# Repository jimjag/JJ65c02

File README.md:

6502 6502 6502 6502 6502 6502 6502 6502 6502 6502 6502 6502 6502 6502 6502 6502 6502
# Introduction

**JJ6502** is my own personal 6502 Single Board Computer (SBC) interpretation of the noteworthy [Ben Eater 6502 Computer](https://eater.net/6502) setup. In addition to Ben's work, I've used code, concepts and inspiration from a number of people, all acknowledged below in the **Credits** section. The ultimate inspirations are the venerable Apple II and the Atari 800 personal computers

This project contains 3 main sections:

* The actual JJ6502 breadboard computer ([Schematics](./Schematics))
* [Software](./Software)
  * The `miniOS` OS menu and ROM bootloader
  * `pico-code` : The Pi Pico (RP2040/RP2350) A/V chip (VGA driver and PS/2 keyboard interface)
  * `x65c02` Emulator
* [Documents](./Documents)

Each section has its own Readme.md and folder under this repo.

## Philosophy

More than anything, I want JJ6502 to have a retro feel. Sure, I'll use modern technology where needed, but I don't want it to be the focus of the project. I want to keep the hardware and software as authentic as possible, while still being able to take advantage of modern tools and techniques where it doesn't impact the feel and spirit of being "retro."

I am therefore putting some restrictions on the project. For example, I am limiting the video output to a 640x480 VGA screen, and the keyboard input to PS/2; graphics are bitmapped. The system is setup to encourage and foster experimentation and innovation.

Basically, I want to keep it simple and fun and recall the early days of 8-bit computing.

## Updates

Keep up to date by following the project on [Hackaday](https://hackaday.io/project/193153-jj65c02) and our [YouTube channel](https://www.youtube.com/playlist?list=PLI32OMXu1rudGl28vJc05QFXHkXWn0A19). Older notes can be found by reading the [History](./HISTORY.md) file, which served as a running log of additions and improvements.

## Pull Requests

If you would like to see any particular feature I would be happy to accept any actual code contributions via Pull Requests, or even Enhancement requests. I am happy to screen, test and merge any valuable PR.

## Contact

You can, of course, contact me via the normal Github development methods, such as Issues, Pull Requests, etc. You can also ping me via [Email](mailto:jimjag@gmail.com) and follow me/DM me on [Twitter](https://twitter.com/jimjag/)

## Credits

* Specific content noted in their respective sections
* All the helpful peeps on reddit r/beneater/

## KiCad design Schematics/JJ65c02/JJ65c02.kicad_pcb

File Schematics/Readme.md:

# JJ6502 : jimjag's 65c02 Breadboard Computer

Based on [Ben Eaters 6502 Computer](https://eater.net/6502), aka BE6502, this is my own take on his system, following in the long trend of others who have found inspiration and fun due to Ben's work.

There is no way that I could do justice to the insightful education that Ben provides in his videos, and so I won't even try. I encourage you to watch Ben's videos to get the background on his setup and his design choices. Only then will my changes make any sense...

Back? Good! Just jump in.

## What's different?

So starting from Ben's design (as of Sept. 2021), here's a partial list of modifications I've made:

* Different memory map, including bankable RAM
* Console terminal
* Dependent on 65c02 chip (not "generic" 6502)
* Added W65c51 ACIA chip and TTL-serial converter.
* Video/Audio/PS2 Keyboard interface via RP2040/RP2350 (Pi Pico)

Let's look at each in more detail.

### Memory Map
Ben's design uses a simple but functional address decoder design for his setup. The issue is that it wastes a _lot_ of memory. When all you have to work with is 64k, shared between RAM, ROM and I/O, each byte is precious.

For me, I wanted as much RAM as possible, then as much ROM as I could have, and just a little bit of I/O space.

The design I came up with requires the use of the ATF22V10C PLD for decoding. With this new address decoder, we get a much more agreeable memory map:

```
 $0000 - $9fff      RAM: 40k
   $0000 - $00ff      RAM: Zero Page
   $0100 - $01ff      RAM: Stack pointer (sp) / Page 1
   $0200 - $03ff      RAM: Bootloader set-aside / Page 2
   $0400 - $9fff      RAM: Runnable code area
   $8000 - $9fff      RAM: Bankable/swappable 8k segment
 $a000 - $afff      IO: 4k
   $a010 - $a01f      ACIA
   $a020 - $a02f      VIA
   $a800              Pi Pico
 $b000 - $ffff      ROM: 20k
```

This allows for a pretty sizable ROM-based loader and even OS, as well as extremely large (for a 6502) RAM-based code.

Because of this, Ben's code will not run unmodified on the JJ6502, but the changes are minimal. And easy.

### 65C02
Ben's design, of course, also uses the 65C02, in fact, the WDC65C02. However his code doesn't use any of the newer opcodes which this later version of the chip provides (like **PHY**). I've decided that as long as we are using the newer chip, we should take not only hardware but software advantage of that. This means, for example, that whatever assembler you use must honor the 65C02 opcode set. For `vasm`, this means you'll need to assemble with `vasm6502_oldstyle -wdc02 -dotdir -Fbin`

### Serial Support
Adding the `W65c51` ACIA chip and the `Max232` TTL-Serial
converter board allows for true RS232 terminal support,
vital for bootloader support.

## Schematics
All schematics are in the `JJ65c02` folder and use `KiCad`.

## Design
The Design Philosophy is based on being as true as possible to the concept of retro computing, while still being practical. We take advantage of modern technology only where it doesn't compromise on the "retro nature" of the system.

For example, as will be noted below, we use a Pi Pico as an I/O support chip. Now the Pico is an extremely powerful microcontroller; one look at the demos associated with the RP2040/2350, especially those around its graphics capability, show that it would be easy and tempting to offload _all_ those functions to the Pico. To me, however, that would be cheating. I wanted the system to be a 6502 which just happens to use a Pi Pico, not a Pi Pico that just happens to have a 6502.

The SBC is based around a WDC65C02, and uses the same pinout as the original 6502, but with the newer 65C02 opcodes. The design also includes a WDC65C22 VIA chip for additional I/O capabilities, and a WDC65C51 ACIA chip for serial support. All these chips support much higher clock speeds than the original 6502, and the system itself runs at 8MHz and at 5Vdc.

As noted, a Pi Pico (actually the Pico 2 at this time), is used to drive the VGA monitor and the PS2 keyboard which serve as the system _console_. PS2 key codes are sent to the 6502 via the VIA chip, but are limited to 7 bits. Since the system is ASCII based, this is not an issue (the reason why we only send 7 bits is due to not having enough GPIO pins on the Pico). The Pico "answers" on the system at address $A200 and uses the full 8 data bits.

Some of the complexity of the design is due to the level mismatch between the 6502 (et.al.) and the Pico, since the Pico itself runs on 3.3Vdc. We could run the 6502 also at 3.3, but that still would not solve all issues. To address this problem, we use line level converters as needed between the 2 voltages. When talking to the Pico, we actually latch the WRITE data, to ensure that the Pico has the time to read and process the data before the DATA bus goes unstable. All communication from the Pico is, as noted, driven by the VIA chip and interupts.

Running at 8Mhz, a standard EEPROM is simply too slow. There are a few ways of handling this, including clock stretching. I opted for using a `SST39SF010` 128K NOR Flash, which behaves like a super fast EEPROM and is programmed the exact same way. The current design however wastes a lot of that memory, since we only use 20K of its 128K capability. ROM banking is a possible future enhancement.

For the RAM, I selected the `AS6C1008` 128K SRAM chip. It is fast enough to easily handling the 8Mhz system clock speed, and provides for extra RAM via banking. The RAM banking itself is determine via the value on `Port B` of the VIA chip, and is user selectable. There are a total of 7 8K banks currently.

A `FT234XD` RS232 chip with USB output is driven by the ACIA chip to provide terminal (or "tty") communication at `19200-8N1` with hardware flow control. Sound output is line level and provided by a standard audio jack. Power is provided by a USBC connector at 5Vdc which is then also converted to 3.3Vdc with the 2 power buses being routed on the board.

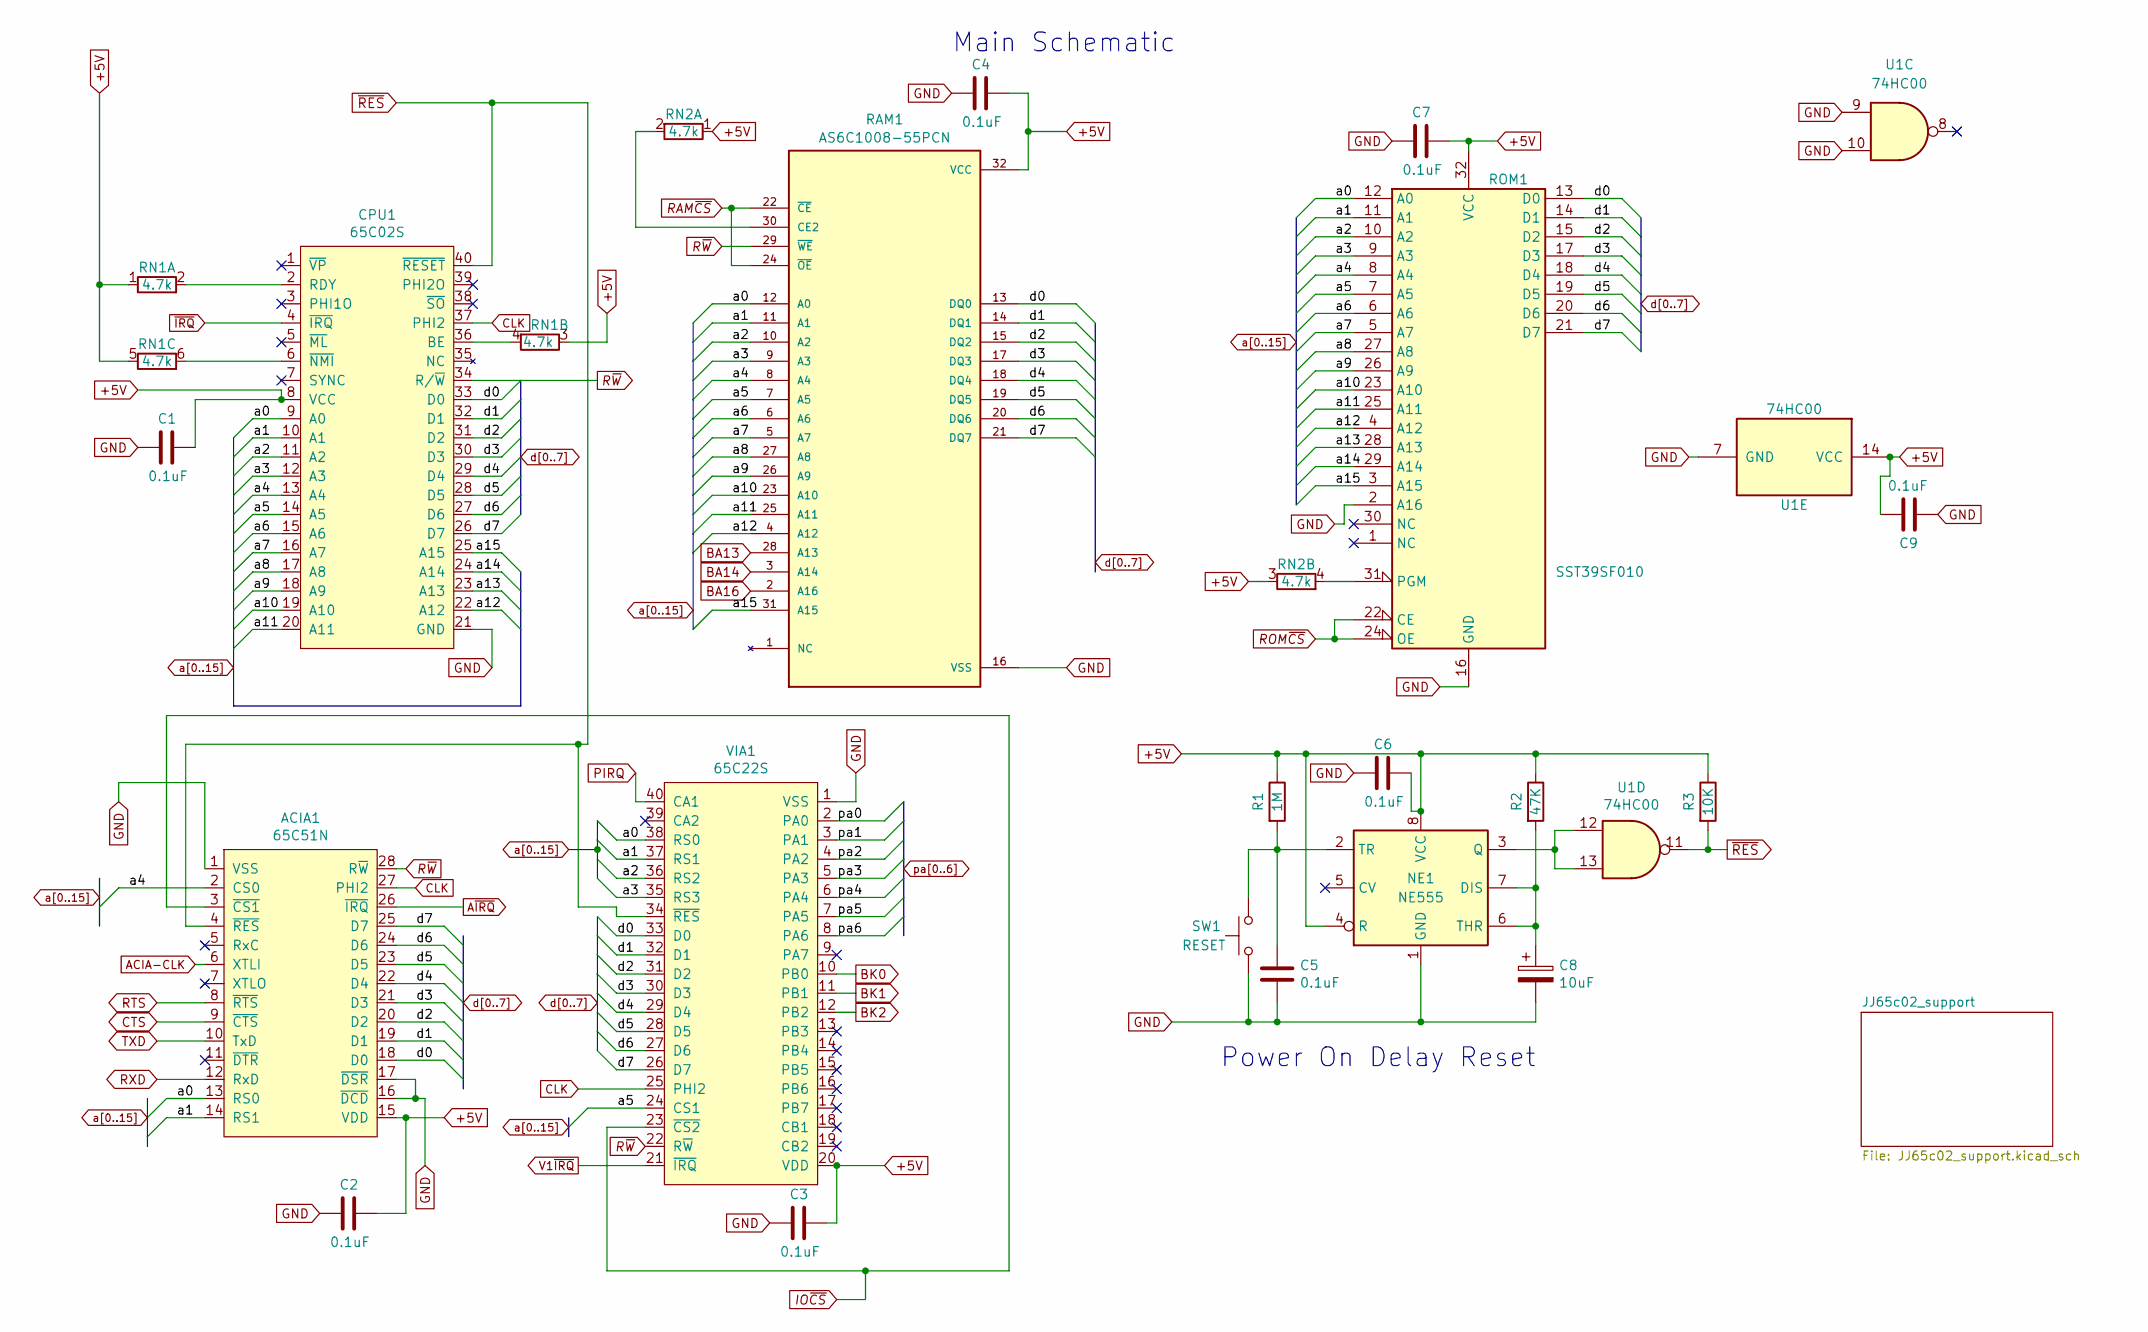
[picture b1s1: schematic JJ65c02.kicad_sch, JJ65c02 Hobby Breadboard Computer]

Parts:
ACIA1: 65C51N; DIP-28_W15.24mm_Socket
C1, C2, C3, C4, C5, C6, C7, C9: 0.1uF; C_Disc_D4.7mm_W2.5mm_P5.00mm
C8: 10uF; CP_Radial_D5.0mm_P2.50mm
CPU1: 65C02S; DIP-40_W15.24mm_Socket
NE1: NE555; DIP-8_W7.62mm
R1: 1M; R_Axial_DIN0207_L6.3mm_D2.5mm_P7.62mm_Horizontal
R2: 47K; R_Axial_DIN0207_L6.3mm_D2.5mm_P7.62mm_Horizontal
R3: 10K; R_Axial_DIN0207_L6.3mm_D2.5mm_P7.62mm_Horizontal
RAM1: AS6C1008-55PCN; DIP-32_W15.24mm_Socket; PARTREV v1.0
RN1, RN2: 4.7k; R_Array_SIP6
ROM1: SST39SF010; DIP-32_W15.24mm_Socket
SW1: RESET; SW_PUSH_6mm
U1: 74HC00; DIP-14_W7.62mm_Socket
VIA1: 65C22S; DIP-40_W15.24mm_Socket

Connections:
+5V: ACIA1.15 (VDD), C1.1, C2.1, C3.1, C4.1, C6.1, C7.1, C9.1, CPU1.8 (VCC), NE1.4 (R), NE1.8 (VCC), R1.1, R2.1, R3.1, RAM1.32 (VCC), RN1.1 (R1.1), RN1.3 (R2.1), RN1.5 (R3.1), RN2.1 (R1.1), RN2.3 (R2.1), ROM1.32 (VCC), U1.14 (VCC), VIA1.20 (VDD); also elsewhere on the board
ACIA-CLK: ACIA1.6 (XTLI); also elsewhere on the board
A~IRQ: ACIA1.26 (~IRQ); also elsewhere on the board
BA13: RAM1.28 (A13); also elsewhere on the board
BA14: RAM1.3 (A14); also elsewhere on the board
BA16: RAM1.2 (A16); also elsewhere on the board
BK0: VIA1.10 (PB0); also elsewhere on the board
BK1: VIA1.11 (PB1); also elsewhere on the board
BK2: VIA1.12 (PB2); also elsewhere on the board
CLK: ACIA1.27 (PHI2), CPU1.37 (PHI2), VIA1.25 (PHI2); also elsewhere on the board
CTS: ACIA1.9 (~CTS); also elsewhere on the board
GND: ACIA1.1 (VSS), ACIA1.16 (~DCD), ACIA1.17 (~DSR), C1.2, C2.2, C3.2, C4.2, C5.2, C6.2, C7.2, C8.2, C9.2, CPU1.21 (GND), NE1.1 (GND), RAM1.16 (VSS), ROM1.2 (A16), ROM1.16 (GND), SW1.1, U1.7 (GND), U1.9, U1.10, VIA1.1 (VSS); also elsewhere on the board
IO~CS: ACIA1.3 (~CS1), VIA1.23 (~CS2); also elsewhere on the board
unnamed: CPU1.36 (BE), RN1.4 (R2.2)
unnamed: CPU1.2 (RDY), RN1.2 (R1.2)
unnamed: CPU1.6 (~NMI), RN1.6 (R3.2)
unnamed: C8.1, NE1.6 (THR), NE1.7 (DIS), R2.2
unnamed: NE1.3 (Q), U1.12, U1.13
unnamed: C5.1, NE1.2 (TR), R1.2, SW1.2
unnamed: RAM1.30 (CE2), RN2.2 (R1.2)
unnamed: RN2.4 (R2.2), ROM1.31 (PGM)
PIRQ: VIA1.40 (CA1); also elsewhere on the board
RAM~CS: RAM1.22 (~CE), RAM1.24 (~OE); also elsewhere on the board
ROM~CS: ROM1.22 (CE), ROM1.24 (OE); also elsewhere on the board
RTS: ACIA1.8 (~RTS); also elsewhere on the board
RXD: ACIA1.12 (RxD); also elsewhere on the board
R~W: ACIA1.28 (R~W), CPU1.34 (R/~W), RAM1.29 (~WE), VIA1.22 (R~W); also elsewhere on the board
TXD: ACIA1.10 (TxD); also elsewhere on the board
V1~IRQ: VIA1.21 (~IRQ); also elsewhere on the board
a0: ACIA1.13 (RS0), CPU1.9 (A0), RAM1.12 (A0), ROM1.12 (A0), VIA1.38 (RS0)
a1: ACIA1.14 (RS1), CPU1.10 (A1), RAM1.11 (A1), ROM1.11 (A1), VIA1.37 (RS1)
a2: CPU1.11 (A2), RAM1.10 (A2), ROM1.10 (A2), VIA1.36 (RS2)
a3: CPU1.12 (A3), RAM1.9 (A3), ROM1.9 (A3), VIA1.35 (RS3)
a4: ACIA1.2 (CS0), CPU1.13 (A4), RAM1.8 (A4), ROM1.8 (A4)
a5: CPU1.14 (A5), RAM1.7 (A5), ROM1.7 (A5), VIA1.24 (CS1)
a6: CPU1.15 (A6), RAM1.6 (A6), ROM1.6 (A6)
a7: CPU1.16 (A7), RAM1.5 (A7), ROM1.5 (A7)
a8: CPU1.17 (A8), RAM1.27 (A8), ROM1.27 (A8)
a9: CPU1.18 (A9), RAM1.26 (A9), ROM1.26 (A9)
a10: CPU1.19 (A10), RAM1.23 (A10), ROM1.23 (A10)
a11: CPU1.20 (A11), RAM1.25 (A11), ROM1.25 (A11); also elsewhere on the board
a12: CPU1.22 (A12), RAM1.4 (A12), ROM1.4 (A12); also elsewhere on the board
a13: CPU1.23 (A13), ROM1.28 (A13); also elsewhere on the board
a14: CPU1.24 (A14), ROM1.29 (A14); also elsewhere on the board
a15: CPU1.25 (A15), RAM1.31 (A15), ROM1.3 (A15); also elsewhere on the board
d0: ACIA1.18 (D0), CPU1.33 (D0), RAM1.13 (DQ0), ROM1.13 (D0), VIA1.33 (D0); also elsewhere on the board
d1: ACIA1.19 (D1), CPU1.32 (D1), RAM1.14 (DQ1), ROM1.14 (D1), VIA1.32 (D1); also elsewhere on the board
d2: ACIA1.20 (D2), CPU1.31 (D2), RAM1.15 (DQ2), ROM1.15 (D2), VIA1.31 (D2); also elsewhere on the board
d3: ACIA1.21 (D3), CPU1.30 (D3), RAM1.17 (DQ3), ROM1.17 (D3), VIA1.30 (D3); also elsewhere on the board
d4: ACIA1.22 (D4), CPU1.29 (D4), RAM1.18 (DQ4), ROM1.18 (D4), VIA1.29 (D4); also elsewhere on the board
d5: ACIA1.23 (D5), CPU1.28 (D5), RAM1.19 (DQ5), ROM1.19 (D5), VIA1.28 (D5); also elsewhere on the board
d6: ACIA1.24 (D6), CPU1.27 (D6), RAM1.20 (DQ6), ROM1.20 (D6), VIA1.27 (D6); also elsewhere on the board
d7: ACIA1.25 (D7), CPU1.26 (D7), RAM1.21 (DQ7), ROM1.21 (D7), VIA1.26 (D7); also elsewhere on the board
pa0: VIA1.2 (PA0); also elsewhere on the board
pa1: VIA1.3 (PA1); also elsewhere on the board
pa2: VIA1.4 (PA2); also elsewhere on the board
pa3: VIA1.5 (PA3); also elsewhere on the board
pa4: VIA1.6 (PA4); also elsewhere on the board
pa5: VIA1.7 (PA5); also elsewhere on the board
pa6: VIA1.8 (PA6); also elsewhere on the board
~IRQ: CPU1.4 (~IRQ); also elsewhere on the board
~RES: ACIA1.4 (~RES), CPU1.40 (~RESET), R3.2, U1.11, VIA1.34 (~RES)

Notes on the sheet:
Main Schematic
Power On Delay Reset

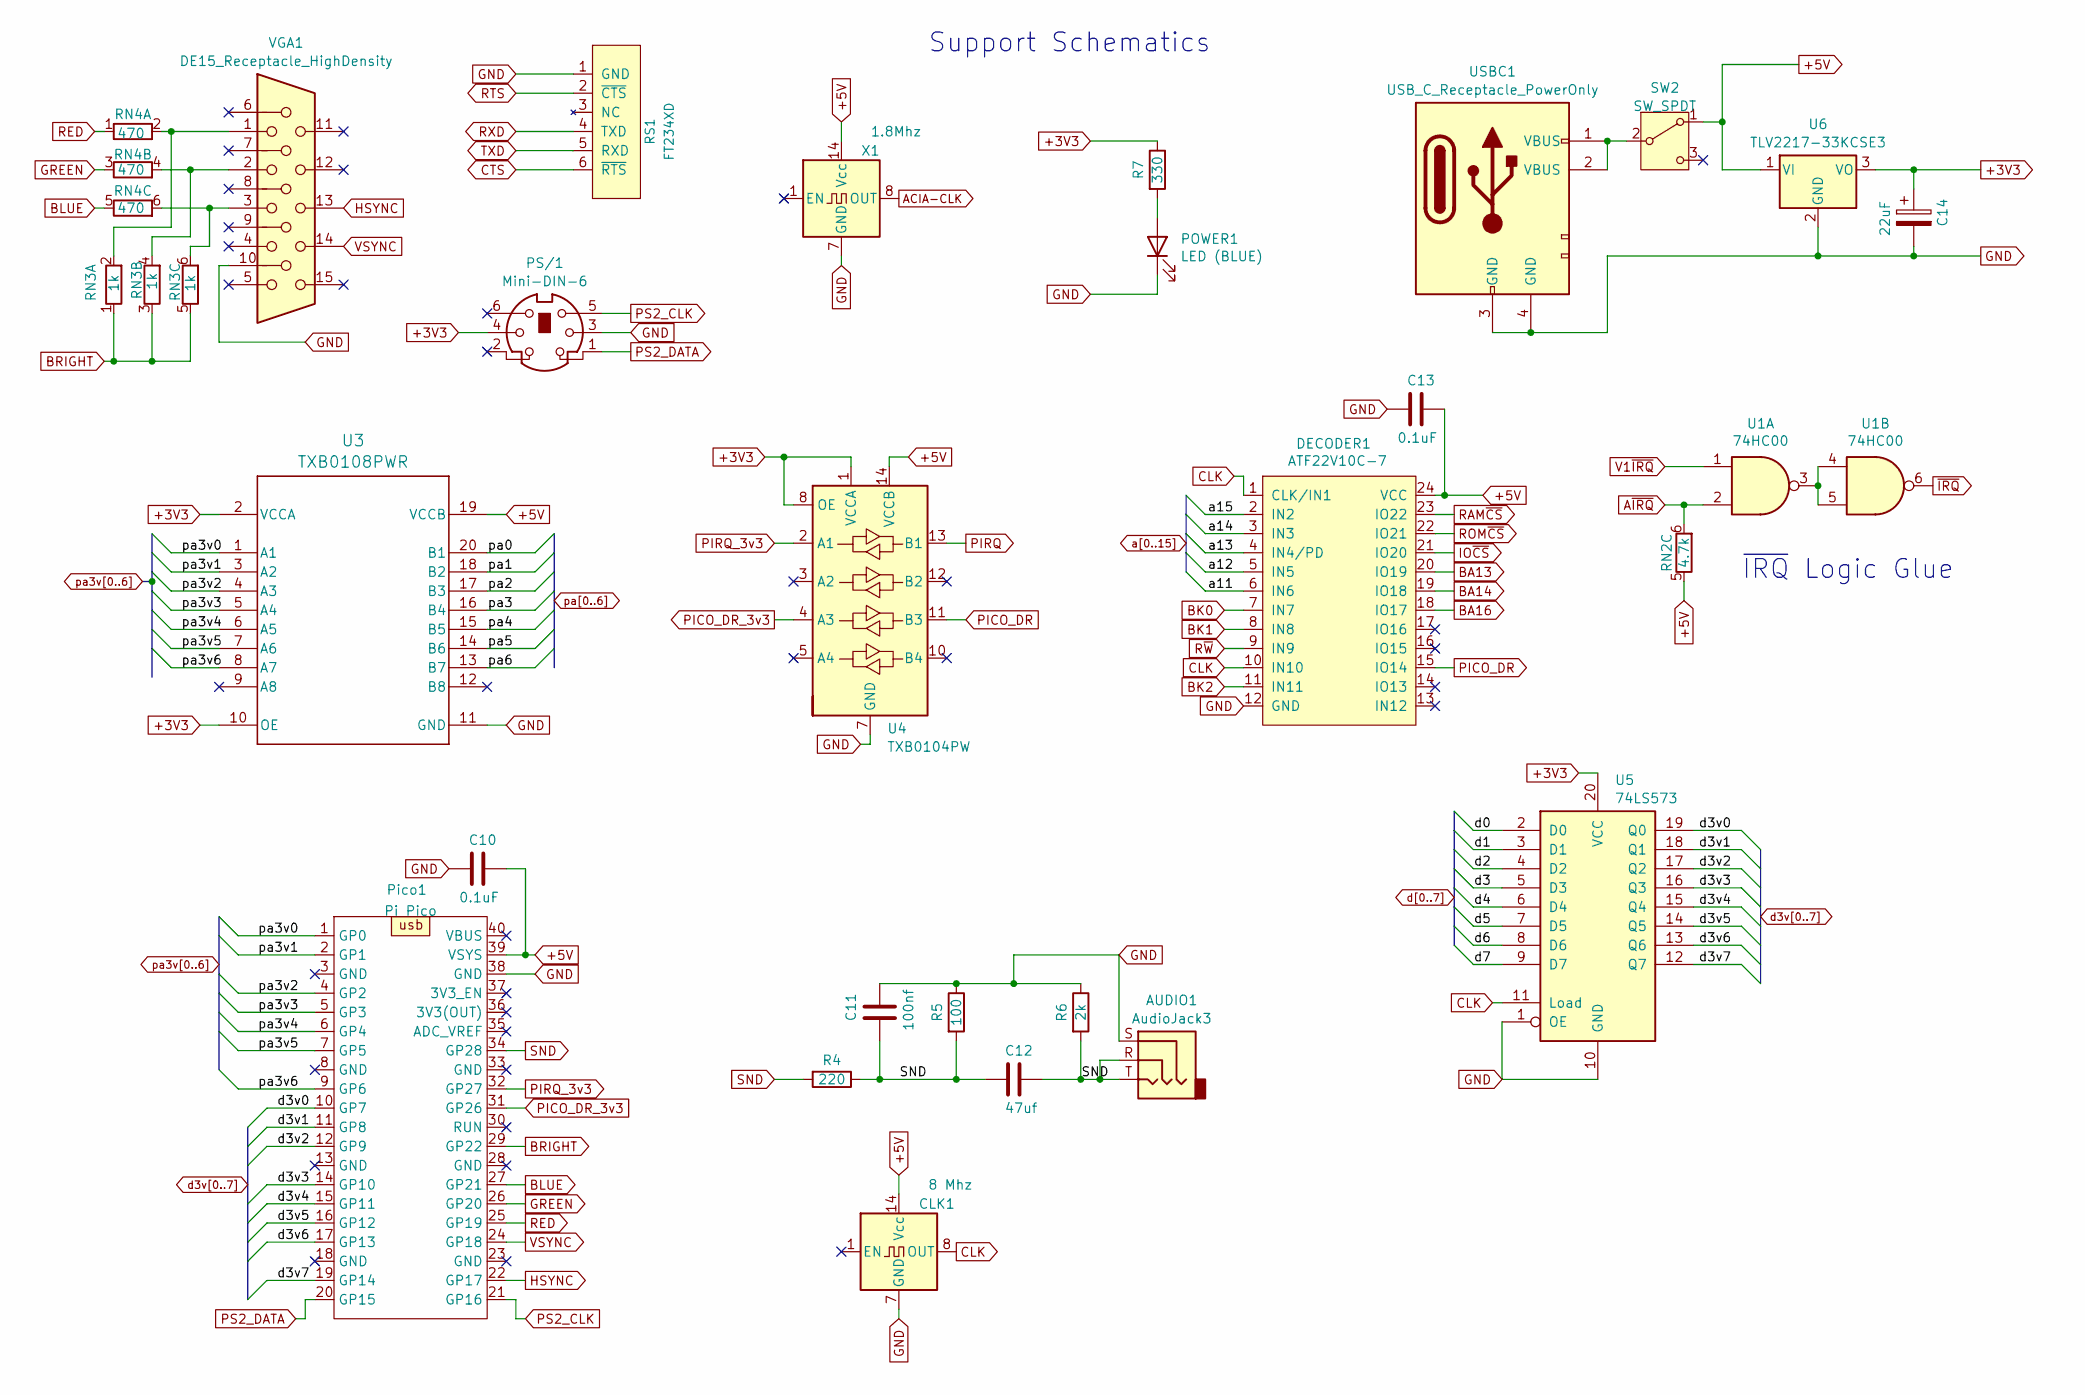
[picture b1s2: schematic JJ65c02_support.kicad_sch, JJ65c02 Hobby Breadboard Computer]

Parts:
AUDIO1: AudioJack3; Jack_3.5mm_CUI_SJ1-3533NG_Horizontal
C10, C13: 0.1uF; C_Disc_D4.7mm_W2.5mm_P5.00mm
C11: 100nf; C_Disc_D4.7mm_W2.5mm_P5.00mm
C12: 47uf; C_Disc_D4.7mm_W2.5mm_P5.00mm
C14: 22uF; CP_Radial_D6.3mm_P2.50mm
CLK1: 8 Mhz; Oscillator_DIP-14
DECODER1: ATF22V10C-7; DIP-24_W7.62mm_Socket
POWER1: LED (BLUE); LED_D3.0mm_FlatTop
PS/1: Mini-DIN-6; mini_din-6
Pico1: Pi Pico; Raspberry_pi_pico
R4: 220; R_Axial_DIN0207_L6.3mm_D2.5mm_P7.62mm_Horizontal
R5: 100; R_Axial_DIN0207_L6.3mm_D2.5mm_P7.62mm_Horizontal
R6: 2k; R_Axial_DIN0207_L6.3mm_D2.5mm_P7.62mm_Horizontal
R7: 330; R_Axial_DIN0207_L6.3mm_D2.5mm_P7.62mm_Horizontal
RN2: 4.7k; R_Array_SIP6
RN3: 1k; R_Array_SIP6
RN4: 470; R_Array_SIP6
RS1: FT234XD; TerminalBlock_TE_282834-6_1x06_P2.54mm_Horizontal
SW2: SW_SPDT
U1: 74HC00; DIP-14_W7.62mm_Socket
U3: TXB0108PWR; TSSOP-20_4.4x6.5mm_P0.65mm
U4: TXB0104PW; SOIC-14_3.9x8.7mm_P1.27mm
U5: 74LS573; SOIC-20W_7.5x12.8mm_P1.27mm
U6: TLV2217-33KCSE3; TO-220-3_Vertical
USBC1: USB_C_Receptacle_PowerOnly; USBC_power
VGA1: DE15_Receptacle_HighDensity; CONN_HDE15P_AMP
X1: 1.8Mhz; Oscillator_DIP-14

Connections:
+3V3: C14.1, PS/1.4, R7.1, U3.2 (VCCA), U3.10 (OE), U4.1 (VCCA), U4.8 (OE), U5.20 (VCC), U6.3 (VO)
+5V: C10.1, C13.1, CLK1.14 (Vcc), DECODER1.24 (VCC), Pico1.39 (VSYS), RN2.5 (R3.1), SW2.1 (A), U3.19 (VCCB), U4.14 (VCCB), U6.1 (VI), X1.14 (Vcc); also elsewhere on the board
ACIA-CLK: X1.8 (OUT); also elsewhere on the board
A~IRQ: RN2.6 (R3.2), U1.2; also elsewhere on the board
BA13: DECODER1.20 (IO19); also elsewhere on the board
BA14: DECODER1.19 (IO18); also elsewhere on the board
BA16: DECODER1.18 (IO17); also elsewhere on the board
BK0: DECODER1.7 (IN7); also elsewhere on the board
BK1: DECODER1.8 (IN8); also elsewhere on the board
BK2: DECODER1.11 (IN11); also elsewhere on the board
BLUE: Pico1.27 (GP21), RN4.5 (R3.1); also elsewhere on the board
BRIGHT: Pico1.29 (GP22), RN3.1 (R1.1), RN3.3 (R2.1), RN3.5 (R3.1); also elsewhere on the board
CLK: CLK1.8 (OUT), DECODER1.1 (CLK/IN1), DECODER1.10 (IN10), U5.11 (Load); also elsewhere on the board
CTS: RS1.6 (~RTS); also elsewhere on the board
GND: AUDIO1.S, C10.2, C11.1, C13.2, C14.2, CLK1.7 (GND), DECODER1.12 (GND), POWER1.1 (K), PS/1.3, Pico1.38 (GND), R5.1, R6.1, RS1.1 (GND), U3.11 (GND), U4.7 (GND), U5.1 (OE), U5.10 (GND), U6.2 (GND), USBC1.3 (GND), USBC1.4 (GND), VGA1.10, X1.7 (GND); also elsewhere on the board
GREEN: Pico1.26 (GP20), RN4.3 (R2.1); also elsewhere on the board
HSYNC: Pico1.22 (GP17), VGA1.13; also elsewhere on the board
IO~CS: DECODER1.21 (IO20); also elsewhere on the board
unnamed: POWER1.2 (A), R7.2
unnamed: RN3.2 (R1.2), RN4.2 (R1.2), VGA1.1
unnamed: RN3.4 (R2.2), RN4.4 (R2.2), VGA1.2
unnamed: RN3.6 (R3.2), RN4.6 (R3.2), VGA1.3
unnamed: SW2.2 (B), USBC1.1 (VBUS), USBC1.2 (VBUS)
unnamed: U1.3, U1.4, U1.5
PICO_DR: DECODER1.15 (IO14), U4.11 (B3)
PICO_DR_3v3: Pico1.31 (GP26), U4.4 (A3); also elsewhere on the board
PIRQ: U4.13 (B1); also elsewhere on the board
PIRQ_3v3: Pico1.32 (GP27), U4.2 (A1); also elsewhere on the board
PS2_CLK: PS/1.5, Pico1.21 (GP16); also elsewhere on the board
PS2_DATA: PS/1.1, Pico1.20 (GP15); also elsewhere on the board
RAM~CS: DECODER1.23 (IO22); also elsewhere on the board
RED: Pico1.25 (GP19), RN4.1 (R1.1); also elsewhere on the board
ROM~CS: DECODER1.22 (IO21); also elsewhere on the board
RTS: RS1.2 (~CTS); also elsewhere on the board
RXD: RS1.4 (TXD); also elsewhere on the board
R~W: DECODER1.9 (IN9); also elsewhere on the board
SND: AUDIO1.R, AUDIO1.T, C11.2, C12.1, C12.2, Pico1.34 (GP28), R4.1, R4.2, R5.2, R6.2; also elsewhere on the board
TXD: RS1.5 (RXD); also elsewhere on the board
V1~IRQ: U1.1; also elsewhere on the board
VSYNC: Pico1.24 (GP18), VGA1.14; also elsewhere on the board
a11: DECODER1.6 (IN6); also elsewhere on the board
a12: DECODER1.5 (IN5); also elsewhere on the board
a13: DECODER1.4 (IN4/PD); also elsewhere on the board
a14: DECODER1.3 (IN3); also elsewhere on the board
a15: DECODER1.2 (IN2); also elsewhere on the board
d0: U5.2 (D0); also elsewhere on the board
d1: U5.3 (D1); also elsewhere on the board
d2: U5.4 (D2); also elsewhere on the board
d3: U5.5 (D3); also elsewhere on the board
d3v0: Pico1.10 (GP7), U5.19 (Q0); also elsewhere on the board
d3v1: Pico1.11 (GP8), U5.18 (Q1); also elsewhere on the board
d3v2: Pico1.12 (GP9), U5.17 (Q2); also elsewhere on the board
d3v3: Pico1.14 (GP10), U5.16 (Q3); also elsewhere on the board
d3v4: Pico1.15 (GP11), U5.15 (Q4); also elsewhere on the board
d3v5: Pico1.16 (GP12), U5.14 (Q5); also elsewhere on the board
d3v6: Pico1.17 (GP13), U5.13 (Q6); also elsewhere on the board
d3v7: Pico1.19 (GP14), U5.12 (Q7); also elsewhere on the board
d4: U5.6 (D4); also elsewhere on the board
d5: U5.7 (D5); also elsewhere on the board
d6: U5.8 (D6); also elsewhere on the board
d7: U5.9 (D7); also elsewhere on the board
pa0: U3.20 (B1); also elsewhere on the board
pa1: U3.18 (B2); also elsewhere on the board
pa2: U3.17 (B3); also elsewhere on the board
pa3: U3.16 (B4); also elsewhere on the board
pa3v0: Pico1.1 (GP0), U3.1 (A1); also elsewhere on the board
pa3v1: Pico1.2 (GP1), U3.3 (A2); also elsewhere on the board
pa3v2: Pico1.4 (GP2), U3.4 (A3); also elsewhere on the board
pa3v3: Pico1.5 (GP3), U3.5 (A4); also elsewhere on the board
pa3v4: Pico1.6 (GP4), U3.6 (A5); also elsewhere on the board
pa3v5: Pico1.7 (GP5), U3.7 (A6); also elsewhere on the board
pa3v6: Pico1.9 (GP6), U3.8 (A7); also elsewhere on the board
pa4: U3.15 (B5); also elsewhere on the board
pa5: U3.14 (B6); also elsewhere on the board
pa6: U3.13 (B7); also elsewhere on the board
~IRQ: U1.6; also elsewhere on the board

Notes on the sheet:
Support Schematics
~{IRQ} Logic Glue

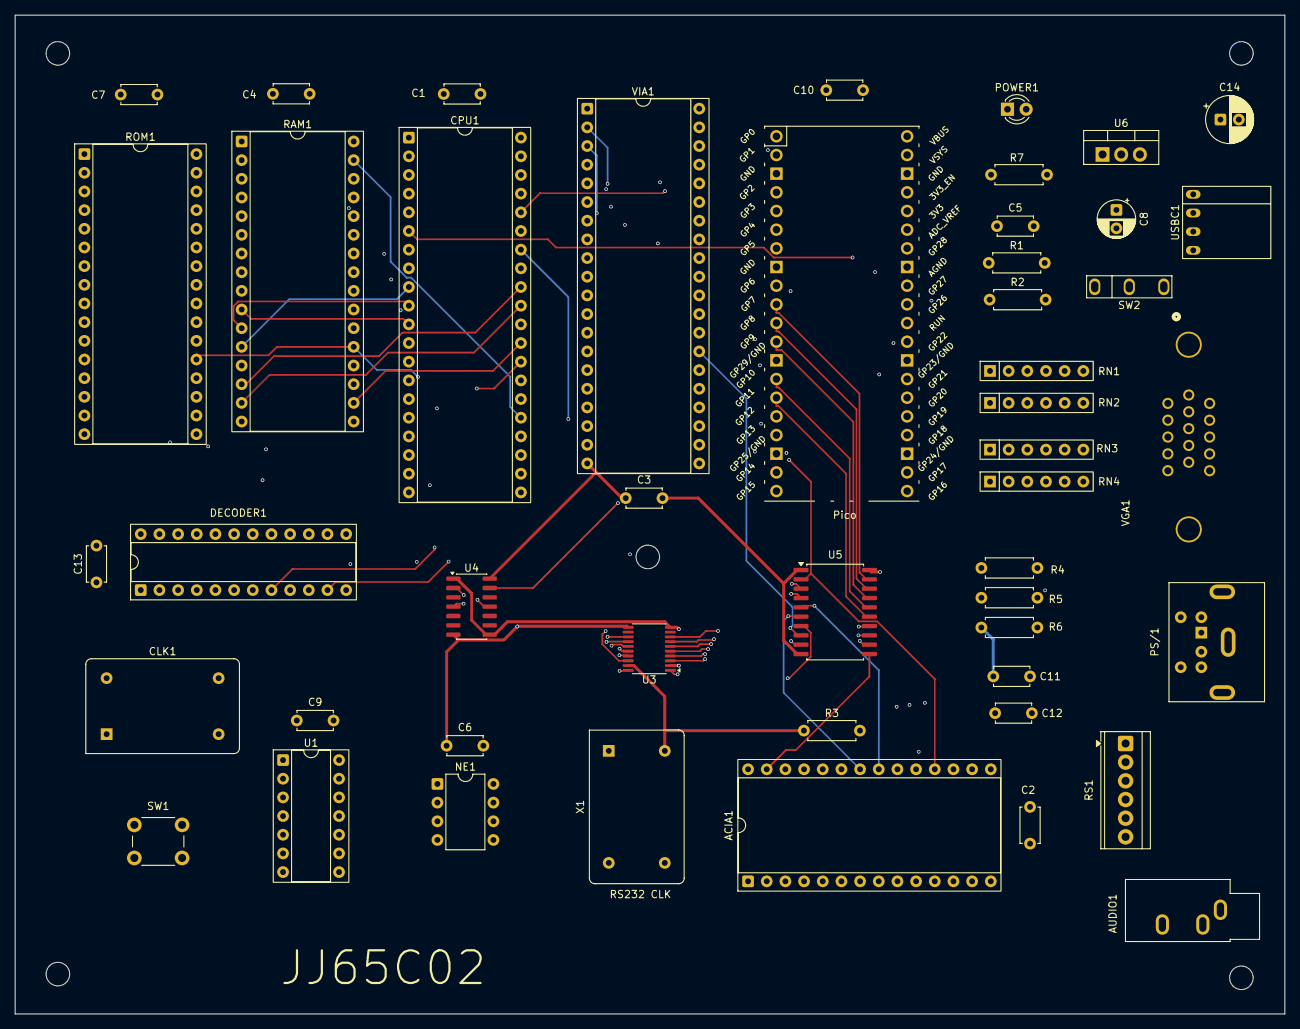
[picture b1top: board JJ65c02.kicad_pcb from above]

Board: 4 copper layers, 172.7 x 135.9 mm, 53 parts (1 on the bottom side), 96 nets.

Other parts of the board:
PH1, PH2, PH3, PH4, PH5: MountingHole_3.2mm_M3_DIN965
Pico: Pico; RPi_Pico_SMD_TH

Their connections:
+5V: Pico.39 (VSYS); also elsewhere on the board
BLUE: Pico.27 (GPIO21); also elsewhere on the board
BRIGHT: Pico.29 (GPIO22); also elsewhere on the board
GND: Pico.38 (GND); also elsewhere on the board
GREEN: Pico.26 (GPIO20); also elsewhere on the board
HSYNC: Pico.22 (GPIO17); also elsewhere on the board
PICO_DR_3v3: Pico.31 (GPIO26_ADC0); also elsewhere on the board
PIRQ_3v3: Pico.32 (GPIO27_ADC1); also elsewhere on the board
PS2_CLK: Pico.21 (GPIO16); also elsewhere on the board
PS2_DATA: Pico.20 (GPIO15); also elsewhere on the board
RED: Pico.25 (GPIO19); also elsewhere on the board
SND: Pico.34 (GPIO28_ADC2); also elsewhere on the board
VSYNC: Pico.24 (GPIO18); also elsewhere on the board
d3v0: Pico.10 (GPIO7); also elsewhere on the board
d3v1: Pico.11 (GPIO8); also elsewhere on the board
d3v2: Pico.12 (GPIO9); also elsewhere on the board
d3v3: Pico.14 (GPIO10); also elsewhere on the board
d3v4: Pico.15 (GPIO11); also elsewhere on the board
d3v5: Pico.16 (GPIO12); also elsewhere on the board
d3v6: Pico.17 (GPIO13); also elsewhere on the board
d3v7: Pico.19 (GPIO14); also elsewhere on the board
pa3v0: Pico.1 (GPIO0); also elsewhere on the board
pa3v1: Pico.2 (GPIO1); also elsewhere on the board
pa3v2: Pico.4 (GPIO2); also elsewhere on the board
pa3v3: Pico.5 (GPIO3); also elsewhere on the board
pa3v4: Pico.6 (GPIO4); also elsewhere on the board
pa3v5: Pico.7 (GPIO5); also elsewhere on the board
pa3v6: Pico.9 (GPIO6); also elsewhere on the board

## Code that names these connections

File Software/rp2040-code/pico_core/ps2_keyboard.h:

#ifndef P2_KEYBOARD_H_
#define P2_KEYBOARD_H_
#include "hardware/clocks.h"
#include "hardware/dma.h"
#include "hardware/pio.h"
#include "hardware/gpio.h"
#include "pico/stdlib.h"
#include <stdio.h>
#include <stdlib.h>

#define PS2FREQ   133600.0f

// GPIO pins to VIA chip
enum ps2_pins {PA0=0, PA1, PA2, PA3, PA4, PA5, PA6, PS2_DATA_PIN=15, PS2_CLK_PIN, PIRQ=27};

void initPS2(void);
unsigned char ps2GetChar(bool auto_print);
unsigned char ps2GetCharBlk(bool auto_print);
void clearPS2(void);
void ps2Task(bool auto_print);

#endif // P2_KEYBOARD_H_

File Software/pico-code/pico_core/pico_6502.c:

/**
 * MIT License
 * Copyright (c) 2021-2024 Jim Jagielski
 */
/**
 *
 * HARDWARE CONNECTIONS
 *  - GPIO 17 ---> VGA Hsync
 *  - GPIO 18 ---> VGA Vsync
 *  - GPIO 19 ---> 470 ohm resistor ---> VGA Red
 *  - GPIO 20 ---> 470 ohm resistor ---> VGA Green
 *  - GPIO 21 ---> 470 ohm resistor ---> VGA Blue
 *  - GPIO 22 ---> 1k ohm resistor ---> VGA Intensity (bright)
 *  - GPIO 15 ---> PS2 Data pin
 *  - GPIO 16 ---> PS2 Clock pin
 *  - RP2040 GND ---> VGA GND
 *  - GPIO 0-6 ---> 7 bit PS/2 Data to VIA
 *  - GPIO 7-14 ---> 8 Bit Data In from 6502
 *  - GPIO 26 ---> Data Ready
 *  - GPIO 27 ---> IRQ/Handshake to VIA for PS/2
 *  - GPIO 28 ---> audio/sound
 *
 * RESOURCES USED
 *  CORE 0
 *  - VGA:
 *  -   PIO state machines 0, 1, and 2 on PIO instance 0
 *  -   DMA channels 0, 1, 2, and 3
 *  -   IRQ 0, 1
 *  -   153.6 kBytes of RAM (for pixel color data)
 *  - PS2:
 *  -   PIO state machine 0 on PIO instance 1
 *  -   IRQ 1
 *  - MEMIN:
 *  -   PIO state machine 1 on PIO instance 1
 *  -   IRQ 0
 *
 * CORE 1
 * - SND:
 * -   PWM
 */

#ifdef HOST_SIM
// Host SDL simulation: the Pico SDK, PS/2 driver and sound synth are replaced
// by the shims in sim/pico_shim.h (see sim/README.md). This is the same file
// the RP2350 runs; only the hardware layer differs.
#include "../sim/pico_shim.h"
#include "vga_core.h"
#include <stdio.h>
#include <stdlib.h>
#else
#include <stdio.h>
#include <stdlib.h>
#include "pico/stdlib.h"
#include "hardware/pio.h"
#include "hardware/dma.h"
#include "pico/multicore.h"
#include "vga_core.h"
#include "ps2_keyboard.h"
#include "pico_synth_ex.h"
#endif

void core1_main() {
    initPS2();
    clearPS2();
    initSOUND();
    startup_chord();
    while (true) {
        soundTask();
        ps2Task(false);
        //tight_loop_contents();
    }
}

#ifdef HOST_SIM
// The SDL viewer owns the process main thread (macOS requires the Cocoa event
// loop there) and runs this on a worker thread instead of main().
int demo_main()
#else
int main()
#endif
{
    // rp2350 will run at 300 Mhz at 1.3 volt
    // vreg_set_voltage (VREG_VOLTAGE_1_30);
    //vreg_set_voltage(VREG_VOLTAGE_1_15);
    set_sys_clock_khz(300000, true);
    // Initialize stdio
    //stdio_init_all();

    // start core 1 threads
    //multicore_reset_core1();
    multicore_launch_core1(&core1_main);
#ifdef HOST_SIM
    // Bring up the unix-socket listener; the x65c02 emulator connects and its
    // $A800 writes start arriving as the 6502 byte stream (see sim/sim_link.c).
    sim_link_start(NULL);
#endif
    // Initialize the VGA screen and PS/2 interface
    initVGA();
    //initPS2();
    //clearPS2();
    setFont(0);
    setTextColor2(WHITE, BLUE);
    setTxtCursor(0, 0);
    vgaFillScreen(BLUE);
    setCursor(65, 0);
    setTextSize(2);
    drawString(VERSION_6502);
    setTextSize(1);
    setTxtCursor(0, 3);
    enableCurs(true);
    //clearPS2();
    while (true) {
        conInTask();  // Look for incoming data
        //ps2Task(false);  // And send out any PS/2 data
        //tight_loop_contents();
    }
}

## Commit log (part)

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2023-11-19 vga_core was getting big... pull out graphics codebase to a sep file and pull it in via overloading #include instead of adjusting the actual build process to compile/link another file... after all, w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
2023-11-19 Fix blinking cursor potential corruption
2023-11-21 Use interrupts and implement a read buffer
2023-11-21 More work on WOZMON o lowercase opcodes o use CONsole I/O o Don't echo input o check for actual interrupt
2023-11-21 Compile WOZMON Remove more LCD stuff and replace w/ console i/o Use asciiz and not actual bytes since we can simply print these now
2023-11-21 Final nibs to get it compiling... likely will NOT work yet :)
2023-11-22 We're not using Terminus
2023-11-22 Make more universal (avoid hard coded magic numbers) Add blocking char/byte read Continue move from mini-keyboard to Console
2023-11-23 For timing purposes, tell the Pico to READ the data (which the 6502 as written) when the DR signal falls, which corresponds to the 6502 clock falling as well. This ensures that the data to be read is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
2023-11-24 Move to using PIO sm for reading data from the 6502
2023-11-24 Note about Tmds on 6502 which makes this dependent on the actual clock speed of the 6502... :(
2023-11-24 Remove fluff
2023-11-26 Interrupt 1. Don't pull-up these pins
2023-11-29 Update mem map for ehbasic
2023-12-08 Timing for reading from 6502 for CON output
2023-12-08 Get menus working w/ prompts and nice screen rendering
2023-12-08 Just in case the INIT does more at some point, let's just dupe it now
2023-12-08 Stability work Adjust WOZMON to output \r\n since we do not auto-adjust this in the Pico/VGA driver
2023-12-09 Make WOZMON work w/ lowercase
2023-12-12 And we will be using both YMODEM send and recv
2023-12-12 Use standard delay func
2023-12-13 Start implement of LOAD and SAVE for EhBasic using YMODEM to do the actual file and xfer work
2023-12-13 some fluff and lint
2023-12-14 Add in a "transparent" color, which is really just a flag to leave the pixel alone
2023-12-19 Start adding 6502 routines for graphics interface to Pi Pico
2023-12-19 Add in color table (as derived from Pi Pico) and export
2023-12-20 Some simplification
2023-12-20 more timing adjs
2023-12-27 Pull in correct ending address
2023-12-27 Misc clean ups
2023-12-27 Use typedefs
2023-12-28 start on sprite
2023-12-28 Avoid magic numbers when possible. Load in full sprite data. TODO: bitmap, mask, etc...
2023-12-28 Initial draw/erase impl. Does not handle any (x,y) error detection/correction nor does it handle cases where only a section of the sprite is "on screen": all or nothing
2023-12-28 Bug fix
2023-12-28 Don't shift at final loop
2023-12-29 Support USB
2023-12-29 Pre-calc shifted bitmap and mask and save some cycles during a critical time
2023-12-29 Optimize :)
2023-12-30 Use logical indexes that align w/ X ccords
2024-01-03 Update NOTICE Update clock freq for sound PWM
2024-01-05 Get cmd from cpu-cpu FIFO
2024-01-05 Start some sound capabilities... TODO: The sound demo part where we read from the PS/2 and do stuff is delaying??
2024-01-11 Adjust demo and add in change of preset ("voice") functionality
2024-01-11 Some minor fluff
2024-01-12 And these are ZP values
2024-01-23 Update to docs to latest rev of board
2024-01-25 instead of "fixing" STR$(), create CSTR$(), which is what other BASICs provide. NOTE: The arg to CSTR$() must be numeric
2024-01-26 Add in case patch
2024-01-26 Some fine-tuning of sound func
2024-01-29 Push beta1
2024-01-29 Some doc updates
2024-01-30 Additional voices
2024-01-31 comment
2024-01-31 y bounds handling... x is a LOT more complex since 1 byte == 2 pixels.
2024-02-01 Sprite works
2024-02-02 Reformat file to standards
2024-02-02 Allow for each voice to have its own sound
2024-02-02 Reformats
2024-02-03 formatting cleanup - no func changes
2024-02-05 variable height sprites
2024-02-05 Simpl the logic
2024-02-06 prep temp for 32pixel sprites and use generic func calls
2024-02-07 "Double" sprites
2024-02-07 Add some comments explaining some nuances of the sprite code
2024-02-07 Move some static data arrays into flash and save SRAM for actual changing data
2024-02-08 rough in tiles
2024-02-11 Only convert if not already converted
2024-02-11 Use enums and avoid magic numbers
2024-02-11 Update w/ new 32b sprite using color pallette
2024-02-13 Hey. We have an ugly tile!
2024-02-14 Bump to 6502 running at 5Mhz
2024-02-14 Enable RAM banking using VIA PortB bits
2024-02-15 minor ups
2024-02-16 Updated schematics for v2-pico
2024-02-18 if we are using the pi pico to generate the clock, we need to level convert from 3.3 to 5v
2024-02-23 Final rename fixes
2024-02-23 Create PIO sm for CLK/PHI signal on GPIO24
2024-02-27 Pico-2 changes (rp2040 now provides clk) and upgrade to Kicad 8.0
2024-02-28 More work on rp2040-version2
2024-02-29 Add in latest schematic
2024-03-11 More work on rp2040 updates
2024-03-15 Some fine tuning...
2024-03-15 Simplify the blinking cursor code... don't do any actually drawing in the timer callback, just update a var that the timer was triggered.
2024-03-15 We are now running at 8Mhz
2024-03-15 restore these for cases where we don't access through PrintChar()
2024-03-19 Rename to make more sense
2024-08-12 pico-sdk 2.0 is out
2024-08-13 Get building again
2024-10-28 Start doc updates
2025-01-21 Latest updates
2025-01-21 Since we support both the 2040 and the 2350, just use the generic 'pico' name
2025-07-09 Latest versions
2025-07-14 Add in required files for Kicad
2025-08-05 Restore
2025-08-05 Make note
2025-08-06 Work on releasing v2.0.0
2026-01-15 Add in WinCUPL files for programming the ATF22V10 PLD
2026-01-15 2 possible values for device depending on minipro version
2026-01-16 Standardize on ca65 syntax and use variables instead of magic numbers
2026-01-16 Rename vars for more logical names
2026-01-16 Save some zeropage memory (7 bytes!) and create a variable for determining where BASIC gets its I/O from
2026-01-16 Clean up ehbasic.c for standard formatting
2026-01-19 And more formatting - no func changes
2026-01-19 correct mistaken comment in string (actually, char)
2026-01-19 Add in 'TTY' command for EhBASIC, which switches the I/O for BASIC from the Console to the Serial Port TTY.
    Expected use:
    Enter TTY
    Use TTY terminal program to cut/paste for file listing or entry
    Enter TTY again
    Back to Console mode
2026-01-19 Some work on getting Emulator to work... if doing emulator (using a 6502 simulator), bypass some junk like checking RAM, etc...
2026-01-20 Work on emulator I/O
2026-01-20 Just sleep to control speed
2026-01-20 formatting
2026-01-20 Finish TTY command
2026-01-21 Final (ha!) touches to get TTY working
2026-01-21 Work on another program loading method: Intel HEX format
2026-01-21 Check for both \r and \n Skip inf loop if we never see a ':' - only check line len and ignore
2026-01-21 Handle branches > 128
2026-01-22 Keep track of how much the _system_ uses of ZP. Consider system usage of ZP memory as protected memory, unavailable for re-use. We may eventually need to reuse ZP memory in large portions.
2026-01-22 Sometimes we need another stack, but it doesn't need to be so big; so create one! Just push/pull the A reg into this mini stack
2026-01-22 Protect against a bad RUN and use 65c02 as applicable
2026-01-23 Some build/make improvements
2026-01-26 Some doc updates to bring everything up to speed
2026-01-27 Be sure to honor the corrupt BASIC FP flag
2026-01-27 Allow for FORTH to also switch between console and tty
2026-01-27 Put all sources needed to make in the actual src dir. Makes it easier when compiling RAM progs
2026-01-28 Avoid using TTY when the ACIA isn't detected and/or enabled
2026-01-28 After testing RAM, null it out and make it all self-contained.
2026-01-28 Add in I/O Vectors for an easy (and stable ABI) write/read JMP table
2026-01-28 Work on updates to the docs in prep for release
2026-01-28 Add in mini wozmon guide
2026-01-29 Design write-up
2026-01-29 Slight re-org of Main Menu.
2026-01-29 Just do char cmp instead of actual value check
2026-01-30 Start testing of porting SUPERMON to JJ65C02. We _know_ we need to totally revamp the opcode stuff for the disassembler (and assembler) since we want to support the full WDC65C02 opcode set, which re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
2026-01-30 Start of support for 65c02 opcodes... Have a map which uses the opcode value as an index to its name and its addressing mode. Re-use the "packed name" variation, since it does save some bytes.
    NOTE: The logic to use this has NOT been folded in yet!!
2026-01-30 Remove left over fluff and increase terminal size to 80x24
2026-02-01 Add in some useful comments
2026-02-02 Add in some building comments and an usage guide
2026-02-02 And fix paths from relative
2026-02-02 More clean-up
2026-02-03 English. Do you speak it
2026-02-05 update commen w/ correct version number
2026-02-09 Allow for hex entry of values w/ extended Esc[z ansi escape sequence...
2026-02-09 Move up the folder
2026-02-09 Update some sprite funcs
2026-02-10 Trigger when in and out of frame using a combo of interupts (when entering the frame) and DMA chaining (when leaving)
2026-02-10 Provide for non-blocking memory ops
2026-02-11 More info about Sprites
2026-02-11 clarification of shifted sprites
2026-02-11 And align w/ formatting
2026-02-13 And fold in smooth left scroll
2026-02-13 Make indepedent of clock freq
2026-02-13 And bump speed a bit
2026-02-16 Enable double buffering for the rp2350
2026-02-16 Add in the new Verite 8x16 font as an option
2026-02-16 Clarification of flag Better descript of func
2026-02-17 framework for simple reply/response _from_ the PICO beyond PS2 ascii codes
2026-02-17 Protect against DB using pi pico
2026-02-17 Remove issues w/ opt. Make sure we are volitile
2026-02-17 Format the dis output a bit w/ an extra space before the actual opcode
2026-02-17 Use bits
2026-02-17 And in support files
2026-02-18 Some cleanups: 1. Use local labels 2. Use 65c02 bit ops
2026-02-19 Add some info about my design philosophy around the project.
2026-02-19 More esc seqs... reorder. Those with more expected use will be lower numbered
2026-02-19 Note pseudo VRAM limitations
2026-02-26 Update w/ newer banking logic
2026-02-26 Schematic changes - Banking
2026-02-27 Add BOM
2026-04-29 Update statement
2026-05-13 Adjust output so that things line up better
2026-05-13 KiCad 10
2026-05-13 Some improvements on making better use of the RP2350
2026-05-18 Revert "We want to improve dbl frame buffer switching here."
    This reverts commit dbf1a02c1caf5c9c8aa029de79951f049be6dc52.
2026-05-18 Another round of sep data field
2026-05-18 Remove the loader mapping
2026-05-18 32 isn't valid
2026-05-20 Test of beam impl
2026-05-20 Update demo
2026-05-20 Revert "Test of beam impl"
    This reverts commit 9701e8f80b3f2c3ac5bea93fba0d9df2699b960a.
2026-05-20 Some updates for Sprite handling and z-layer
2026-05-20 Work on adding in esc seq for all remaining impls
2026-05-20 And more graphic prims...
2026-05-20 Update so that we don't switch buffers at all, we just update the show from the draw
2026-05-21 Improve the masking and bit shifting implementation for performance and bug fixes
